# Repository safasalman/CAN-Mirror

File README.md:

CAN-Mirror
==========

The CAN Mirror is a one-way CAN traffic repeater. It reads traffic from CAN Bus A and repeats it on CAN Bus 2.

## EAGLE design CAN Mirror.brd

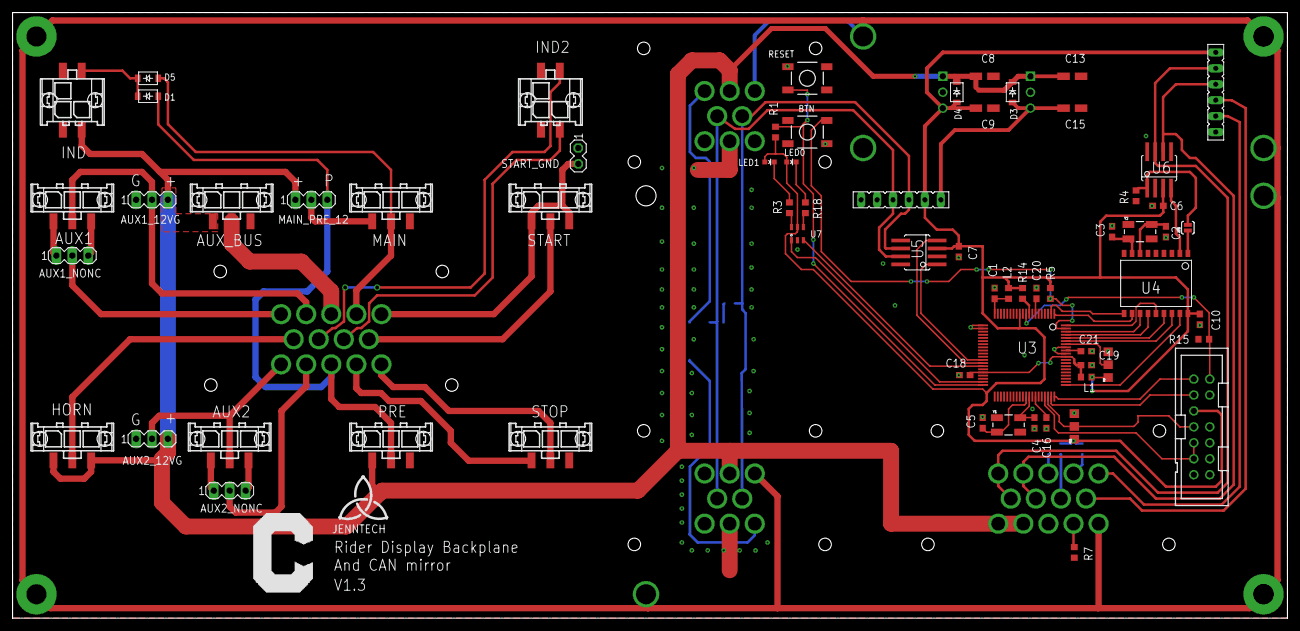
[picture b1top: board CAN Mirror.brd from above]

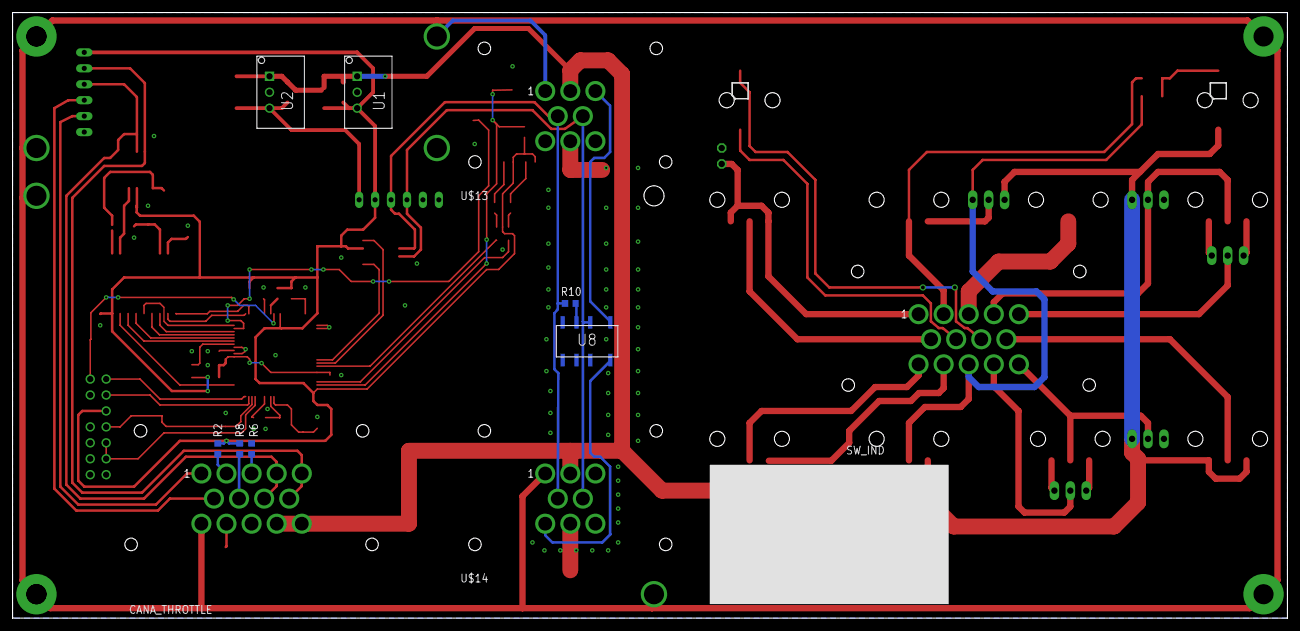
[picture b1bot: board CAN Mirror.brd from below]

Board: 2 copper layers, 203.2 x 96.5 mm, 85 parts (11 on the bottom side), 75 nets.

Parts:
AUX1, AUX2: 43650-0321
AUX1_12VG, AUX1_NONC, AUX2_12VG, AUX2_NONC: MA03-1
AUX_BUS: 43650-0321
BTN: SWITCH-MOMENTARY-2SMD; TACTILE_SWITCH_SMD
C1, C16, C18, C19, C20, C21: 2.2uf; C0603
C2, C3, C4, C5: 8pf; C0603
C6, C7, C10: .1uf; C0603
C8, C9, C13, C15: 10uf; CT3216
CANA_THROTTLE: AMPSEAL_14_7762XX; 776262-1_AMPSEAL_14_VERT
D1, D3, D4, D5: DIODE; SOD-123
HORN: 43650-0321
IND, IND2: 43045-0415
JP5: SJ_2S-NO
L1: 60ohm 1.5A ferrite; R0603
L2: 220ohm ferrite; R0603
LED0, LED1: LED-0603
MAIN: 43650-0321
MAIN_PRE_12: MA03-1
PRE: 43650-0321
R1, R5, R14, R15: 2k2; R0603
R2, R6, R7, R8: 0; R0603
R3, R18: 300; R0603
R4: 5k; R0603
R9, R11: 0603-JUMPER-3WAY
R10: 120; R0603
RESET: SWITCH-MOMENTARY-2SMD; TACTILE_SWITCH_SMD
RIDER_CONTROLS: RIDER_CONTROLS
RIDER_DISPLAY: RIDER_DISPLAY; DISPLAY_BOARD
START_GND: MA02-1
START_SW: 43650-0321
STOP: 43650-0321
SW_IND: AMPSEAL_14_7762XX; 776262-1_AMPSEAL_14_VERT
U1: RECOM_DCDC3v3; INNOLINE-SIP
U2: RECOM_DCDC5v; INNOLINE-SIP
U3: TMS320F28034PNT; PQFP-80_(S-PQFP-G80)
U4: MCP2515; SO-18W
U5, U6: SN65HVD230; SOIC8
U7: SN74LVC2G07DBV; SOT-6_DDC
U8: CAN_Term; IM_RELAY
U$1: CURRENT-LOGO-0.5"; CURRENT-0.5"
U$5, U$7, U$8, U$11: MOUNT_HOLE; MOUNT_HOLE_125
U$6: TI_JTAG14; PAK100/2500-14
U$9, U$12, U$16, U$17: CURRENT-FRAME-LETTER-LANDSCAPE; BLANK
U$13, U$14: CANBUS2VERT; 776276-1_AMPSEAL_8_VERT
U$20: SIG
Y1: 10MHz; CRYSTAL-SMD-5X3
Y2: 20MHz; CRYSTAL-SMD-5X3

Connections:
!INT: U3.78, U4.12
!RX0BF: U3.1, U4.11
!RX1BF: U3.2, U4.10
!XRS: R14.2, U3.9
+3V3: C6.1, C7.1, C9.+, C10.1, D4.A, L1.2, L2.2, LED0.A, LED1.A, R1.1, R2.1, R5.1, R8.2, R9.B, R11.B, R14.1, RIDER_CONTROLS.6, RIDER_DISPLAY.2, U1.P$3, U3.12, U4.18, U5.3, U6.3, U7.5, U$6.5
+5V: C15.+, D3.A, RIDER_DISPLAY.1, U2.P$3
+12V: AUX1_12VG.3, AUX2_12VG.3, AUX_BUS.P$1, C8.+, C13.+, CANA_THROTTLE.13, CANA_THROTTLE.14, D3.C, D4.C, HORN.P$1, HORN.P$3, IND.P$1, MAIN_PRE_12.1, PRE.P$1, U1.P$1, U2.P$1, U$13.2, U$14.2
AUX1_C_12_G: AUX1.P$2, AUX1_12VG.2, SW_IND.4
AUX1_NONC: AUX1_NONC.2, SW_IND.5
AUX2_C_12_G: AUX2.P$2, AUX2_12VG.2, SW_IND.14
AUX2_NONC: AUX2_NONC.2, SW_IND.13
AUX_BUS+12: AUX_BUS.P$2, SW_IND.3
BTN: BTN.3, R5.2, U3.79
CANH_2: RIDER_DISPLAY.4, U5.7, U8.2, U$13.5, U$14.5
CANH_A: CANA_THROTTLE.5, CANA_THROTTLE.9, RIDER_CONTROLS.5, U6.7
CANL_2: R10.1, RIDER_DISPLAY.3, U5.6, U$13.4, U$14.4
CANL_A: CANA_THROTTLE.4, CANA_THROTTLE.8, RIDER_CONTROLS.4, U6.6
CAN_!CS: U3.75, U4.16
CAN_!RST: U3.61, U4.17
CAN_SCK: U3.77, U4.13
CAN_SI: U3.80, U4.14
CAN_SO: U3.76, U4.15
GND: AUX1_12VG.1, AUX2_12VG.1, BTN.1, C1.2, C2.2, C3.2, C4.2, C5.2, C6.2, C7.2, C8.-, C9.-, C10.2, C13.-, C15.-, C16.2, C18.2, C19.2, C20.2, C21.2, CANA_THROTTLE.12, IND.P$2, IND.P$4, IND2.P$2, IND2.P$4, R4.2, R6.1, R7.2, R9.C, R11.C, R15.2, RESET.1, RIDER_CONTROLS.1, RIDER_DISPLAY.5, RIDER_DISPLAY.6, START_GND.1, U1.P$2, U2.P$2, U3.8, U3.21, U3.22, U3.35, U3.53, U3.71, U3.73, U4.9, U5.2, U5.8, U6.2, U6.8, U7.2, U$6.8, U$6.10, U$6.12, U$13.7, U$14.7
GPIO34: R9.A, U3.74
HORN_12V: HORN.P$2, SW_IND.9
HV_IND: D1.C, D5.C, IND.P$3
IND_1: IND2.P$1, SW_IND.7
IND_2: IND2.P$3, SW_IND.8
JTAG_!TRST: R15.1, U3.10, U$6.2
JTAG_TCK: U3.57, U$6.9, U$6.11
JTAG_TDI: U3.59, U$6.3
JTAG_TDO: R11.A, U3.58, U$6.7
JTAG_TMS: U3.60, U$6.1
LED0: U3.34, U7.3
LED1: U3.39, U7.1
MAIN_CONT: D5.A, MAIN.P$2, SW_IND.2
unnamed: C3.1, U4.8, Y2.1
unnamed: C2.1, U4.7, Y2.3
unnamed: AUX1.P$1, AUX1_NONC.1
unnamed: JP5.2, R4.1, U6.1
unnamed: AUX1.P$3, AUX1_NONC.3
unnamed: C1.1, L2.1, U3.20
unnamed: R18.2, U7.4
unnamed: AUX2.P$1, AUX2_NONC.1
unnamed: R3.2, U7.6
unnamed: AUX2.P$3, AUX2_NONC.3
unnamed: R10.2, U8.3
unnamed: MAIN.P$1, MAIN_PRE_12.2
unnamed: C18.1, C19.1, L1.1, U3.36, U3.70
unnamed: R1.2, RESET.3, U3.40
unnamed: CANA_THROTTLE.2, R2.2
unnamed: CANA_THROTTLE.3, R6.2
unnamed: CANA_THROTTLE.11, R7.1
unnamed: CANA_THROTTLE.7, R8.1
unnamed: C16.1, U3.54
unnamed: C20.1, U3.7
unnamed: C21.1, U3.72
unnamed: LED1.C, R3.1
unnamed: LED0.C, R18.1
PRECHARGE: D1.A, MAIN_PRE_12.3, PRE.P$2, SW_IND.12
RELAY+: U8.1, U$13.3
RELAY-: U8.8, U$14.6
RXCAN0: U3.33, U5.4
RXCAN1: U4.2, U6.4
SHIELD: CANA_THROTTLE.10, RIDER_CONTROLS.S1, RIDER_CONTROLS.S2, RIDER_CONTROLS.S3, RIDER_CONTROLS.S4, RIDER_DISPLAY.7, RIDER_DISPLAY.8, RIDER_DISPLAY.9, U$5.P$1, U$7.P$1, U$8.P$1, U$11.P$1, U$13.1, U$14.1
START_GND: START_GND.2, START_SW.P$1, START_SW.P$3, SW_IND.1
START_NO: START_SW.P$2, SW_IND.6
STOP_COM: STOP.P$2, SW_IND.10
STOP_NC: STOP.P$1, SW_IND.11
THROTTLE1: CANA_THROTTLE.6, RIDER_CONTROLS.3
THROTTLE2: CANA_THROTTLE.1, RIDER_CONTROLS.2
TXCAN0: U3.32, U5.1
TXCAN1: JP5.1, U4.1
X1: C4.1, U3.52, Y1.3
X2: C5.1, U3.51, Y1.1

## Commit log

2014-11-10 Bring version 1.3 into source control.
2014-11-19 New CAN mirror files
2014-11-24 Can Mirror schematic - incomplete
2014-11-27 Made an awesome board. Initial rev for the updated CAN Mirror on RW3.
2014-11-28 Update board with fixes from Molex.lbr.
2014-11-28 Reroute signals from CAN connectors.
2014-11-28 Finish other routing and add polygons. THIS VERSION PASSES DRC
2014-11-28 add PDF of schematic
2014-11-28 add the rest of the pages of the schematic
2014-11-28 Correct "!CAM_xxx" naming errors on sheet 2 which caused IC7 SPI interface not to be connected
2014-11-28 Route CAN controller lines
2014-11-28 Finalize PCB routing. THIS VERSION PASSES DRC AGAIN
2014-11-29 Add silkscreen labels and Current C logo.
2014-11-29 Move mounting holes to be on metric grid and to ensure screw heads clear connectors.
2014-11-29 Change overall dimensions to 8.7 x 4.0 cm.
2014-11-29 Add board label
2014-11-30 Move some silkscreen text to fit on board
2014-11-30 Associated PARTNO's with every part on the board. Created a BOM and Gerber files. Gerbers are zipped up and ready to go.
2014-11-30 Revert "Update PCB to version 2."
2014-12-01 Remove old CAN Mirror Gerbers. Add title to drawing. Clean up directory.
2015-02-09 MCAD files for CAN mirror from Aaronn Sergent

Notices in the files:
parts and their libraries:
SparkFun: Licensing: CC v3.0 Share-Alike You are welcome to use this library for commercial purposes.
